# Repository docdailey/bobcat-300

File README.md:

# bobcat-300

Repurposing the **Bobcat Miner 300** (board **G285-V1.0**, Rockchip **RK3566**, mini-PCIe LoRa concentrator) from a
Helium hotspot into an open, hackable LoRa node for **time transfer** experiments, the goal being two-way LoRa
time transfer between nodes, validated against GNSS PPS.

*The [stack adapter](stack-adapter/): plugs into the G285 concentrator socket and carries a RAK5146 (SX1303 + GPS) on top.*

Everything here is fact-checked. Every claim in `docs/` ends with a tag:

- **[VERIFIED: source]**: checked against a primary source (code, device tree, datasheet, logic-analyzer capture, meter
  reading or command output, named in the tag)
- **[UNVERIFIED: origin]**: from notes, community pages or inference, not yet confirmed
- **[CONTRADICTED: what disagrees]**: sources disagree; both sides recorded

Each doc ends with a *Contradictions & open questions* section. Corrections are welcome (open an issue with evidence).

## Contents

| Doc | What it covers |
|---|---|
| [docs/os-boot-gpio.md](docs/os-boot-gpio.md) | Armbian on SD (eMMC untouched), boot chain and boot-script gotchas, 1.5 Mbaud debug console, Ethernet (YT8512B) and Wi-Fi quirks, radio power/reset GPIOs, SPI1, SARADC, broken DT nodes, RTC, PTP |
| [docs/bare-metal-rust.md](docs/bare-metal-rust.md) | Bare-metal Rust image for the RK3566 (QEMU-tested), the carved-core-3 Rust PPS engine that runs on hardware, the deployed Linux time-transfer logger, measured results and lessons |
| [docs/gnss-populate.md](docs/gnss-populate.md) | The unpopulated u-blox NEO-footprint GNSS site: pinout, parts to fit and where, antenna path, PPS routing, beep-test results, install plan, risks |
| [docs/socket-pinout-rak5146.md](docs/socket-pinout-rak5146.md) | The **non-standard** concentrator socket pinout (proven with a logic analyzer), why a RAK5146 reads `0xFF` in a stock G285, and the interposer spec |
| [docs/pps-uart-qerr.md](docs/pps-uart-qerr.md) | GPS PPS to the processor (R47P → GPIO4_D0) and its core-3 capture, the RAK GPS UART (pins 31/33, unmapped), and qErr sawtooth correction |
| [stack-adapter/](stack-adapter/) | **Rev B:** Mini Card-sized stack adapter that lets a RAK5146 (SX1303 + GPS) run in the G285 socket; the RAK stacks right on top (routed, DRC-clean review release) |
| [interposer-rev-a/](interposer-rev-a/) | Rev A breakout interposer (50 × 109.5 mm, superseded by the stack adapter) |
| [tools/](tools/) | Small scripts used for the work (see below) |

## Key facts at a glance

- **Concentrator socket SPI (G285):** SCK = **3**, MISO = **5**, MOSI = **6**, CS = **7**. A RAK2287/RAK5146-style card
  expects 45/47/49/51, so it cannot talk in a stock G285 without rerouting. Power (2/24/39/41/52) and ground match.
- **Radio control GPIOs (Linux sysfs numbers on the Armbian 6.18 image):** 125 = GPIO3_D5 RF enable, 122 = GPIO3_D2 power,
  149 = GPIO4_C5 reset. SPI1 (`spi1m1`) → `/dev/spidev1.0`.
- **Debug console:** UART2 at **1,500,000 baud** (not 115200).
- **Stock card:** N3504S (SX1302 + 2× SX1250). SX1302 has no fine timestamp; SX1303 (e.g. RAK5146) does.
- **GNSS:** an empty 24-pad u-blox NEO footprint whose TIMEPULSE pad reaches socket pin 19 through an unfitted resistor.
  **Do not bridge it if a RAK5146 is fitted**, because its GPS drives pin 19 itself.

## Tools

| File | Purpose |
|---|---|
| `tools/reset_lgw.sh` | Radio power/reset sequence for the G285, matching the stock firmware (used by Semtech `sx1302_hal`) |
| `tools/hal-bobcat.patch` | `sx1302_hal` V2.1.0 patch: runs without the STTS751 temperature sensor the G285 lacks, and prints the chip model (SX1302 vs SX1303) |
| `tools/pinscan.py` | Read-only GPIO input scanner (reads each bank's input register via `/dev/mem`) to map pads to SoC pins |
| `tools/stim.py` | Logic-analyzer stimulus: SPI1 test pattern bursts plus a slow reset toggle |
| `tools/chiploop.sh` | Repeated `chip_id` reads for capturing live MISO traffic |

## Safety

- Work with the stock eMMC untouched: boot Armbian from SD. Pull the card to get the stock firmware back.
- The concentrator can transmit at up to 27 dBm. Keep an antenna or load attached, and observe your local regulations.
- Socket tails are 0.8 mm pitch. Power off before probing with anything that can bridge pins.

## Credits and references

- Armbian image for the G285: sicXnull/Bobcat-Armbian.
- Community pinout reference: helium-repurposed.deobfuscated.org, *Devices / Bobber / Bobcat Miner 300*.
- Semtech `sx1302_hal`; RAKwireless RAK5146 datasheet; u-blox NEO-M8 datasheet and hardware integration manual.

## License

MIT (see [LICENSE](LICENSE)), except `tools/hal-bobcat.patch`, which modifies Semtech's `sx1302_hal` and stays under
Semtech's Revised BSD License.

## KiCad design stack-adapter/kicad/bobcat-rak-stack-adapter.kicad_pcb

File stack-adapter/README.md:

# G285 → RAK5146 stack adapter (rev B)

**Status: routed and KiCad-DRC-clean (review release, 2026-10-22). Not yet fabricated or tested; check everything before ordering.**

A Mini Card-sized stack adapter. Its gold fingers plug into the Bobcat G285 concentrator socket. A mini-PCIe socket sits on top,
right behind the fingers, so the RAK5146 card lies directly above the adapter, over the Bobcat's own card area. There is no
breakout and no jumper field. Rev A, the large breakout interposer, is in [../interposer-rev-a/](../interposer-rev-a/).

## Why

The G285 socket carries SPI on pins 3/5/6/7. RAK's cards expect it on 45/47/49/51. The pinout was proven with a logic
analyzer; see [../docs/socket-pinout-rak5146.md](../docs/socket-pinout-rak5146.md).

## Electrical

| Bobcat (fingers) | RAK5146 (socket J1) | Treatment |
|---|---|---|
| 3 SCK | 45 | rerouted |
| 5 MISO | 47 | rerouted |
| 6 MOSI | 49 | rerouted |
| 7 CS | 51 | rerouted |
| 2, 24, 39, 41, 52 | same | 3.3 V, all tied, 0.25 mm traces |
| 4, 9, 15, 18, 21, 26, 27, 29, 34, 35, 37, 40, 43, 50 | same + socket tabs | GND, routed plus F/B pours, 131 stitching vias |
| 22 | 22 (RAK reset, active high) | straight through (sits low = RAK running) |
| **47** (SoC GPIO4_D0) | **19** (RAK GPS PPS out, 3.3 V) | **GPS PPS via R47P, 0R, FITTED** |
| 45 (SoC GPIO4_C7) | 19 (RAK GPS PPS out) | alternate PPS via R45P, 0R, DNP |
| 19 | 19 | **not connected.** DNP 0R option R19 (straight through) |
| 23 | 23 (RAK GPS reset in) | **not connected.** DNP 0R option R23 |
| 30, 31, 32, 33 | same (RAK GPS I2C / UART) | not connected. DNP 0R options R30–R33 |
| everything else | — | not connected on either side |

**GPS PPS: RAK19 → R47P → finger 47 → GPIO4_D0.**
- The GMAC1 PHC has no programmable pins (`pps_available=0`), so PPS has to land on a SoC GPIO.
- Bobcat socket pins 45 and 47 are spare SoC inputs (GPIO4_C7 / GPIO4_D0). That was verified by a read-only EXT_PORT scan with a
  1 kΩ pull on 2026-10-22.
- On the adapter, fingers 45 and 47 are their own nets (F45, F47). They are **not** the RAK's 45/47: those come from the SPI
  reroute of fingers 3 and 5.
- With R19 and R45P open, the RAK-19 net is exactly J1.19, R47P, R45P and R19. Only R47P is fitted, so it reaches finger 47 and
  nothing else (checked on the final netlist). Fit R45P instead of R47P to use GPIO4_C7.

All links are 0402 0R, UNI-ROYAL 0402WGF0000TCE (LCSC C17168, a JLCPCB basic part). On every link, pad 1 is the Bobcat finger and
pad 2 the RAK socket pin.

## Mechanical (all distances from the finger edge)

| Item | Value | Source |
|---|---|---|
| Outline | **60.30 × 30.00 mm**, 31.30 mm across the socket-tab ears (3.20–7.90 mm) | this design |
| Thickness / fingers | 1.0 mm, contacts 0.60 × 2.55 on 0.80, odd contacts on top (verified on a real card) | PCI-SIG Mini CEM 1.2 |
| Bobcat hold-down holes | Ø2.6 at **48.05**, x ±12.10 | Mini CEM fig 2-3 |
| RAK socket J1 | SOFNG PCIE-52P52H (LCSC C444927), top side; pin N at the same x as finger N | |
| J1 card-edge line (where the RAK card's edge seats; the peg line) | **9.30** | footprint + Mini CEM host-socket datum |
| J1 front (odd-row pads, solder tabs) | **4.20**, i.e. **1.65 mm past the 2.55 mm fingers**; J1 body from 5.50 | see "How close" |
| RAK standoff holes | Ø2.4 NPTH at **57.35** (9.30 + 48.05), x ±12.10 | Mini CEM fig 2-3 |
| RAK card far end | 9.30 + 50.95 = **60.25** | |
| Hold-down keep-outs | 5.8 × 5.8 mm, all layers, at every hole | Mini CEM fig 2-7 |
| Bottom side | flat: no components, fingers + routing + GND only | |

**How close the socket can sit to the fingers.** Three limits apply. The third one binds:

1. **Spec.** Mini CEM 1.2 fig 2-7 has a top-side "component keep out area for connector" of **3.20 mm MIN** from the edge, and
   4.20 mm only behind the key slot. Fig 2-9 shows the host connector housing reaching 3.20 mm MAX onto the card.
2. **Fab.** JLCPCB's gold-finger rules set no finger-to-pad spacing. They require only:
   - a full solder-mask opening on the fingers
   - no copper in the bevel
   - the 50 mm minimum size

   The fab profile's general rules still apply: 0.127 mm pad to pad, 0.30 mm copper to edge. J1's solder tabs sit over the
   card's corner notches (edge at 3.20 mm), so the tab front must be at ≥ 3.50 mm. That gives S ≥ 8.6 mm.
3. **Routing escape (binding).** These top fingers have to leave sideways:
   - SPI 3/5/7
   - the PPS fingers 45/47
   - the option fingers 19/23/31/33

   Each needs a via between its end (2.55 mm) and J1's pads, and the bottom fingers' traces (MOSI 6) must pass between those
   vias. Freerouting completes at **S = 9.30** (pads at 4.20). At S = 9.1 / 9.0 / 8.8 / 8.6 it leaves 1 / 1 / 4 / 4 nets
   unrouted after pours.

   Pre-placing the escape vias in a 0.95 mm gap was also tried. Those through vias land among the bottom fingers and wall in
   MOSI 6, so it doesn't work.

**Fit inside the G285.** The space measured past a stock card is 17 mm, so the stack must end within 50.95 + 17 = 67.95 mm of the
finger edge. Seating depth is already inside the numbers above:

- The adapter's fingers seat in the Bobcat socket exactly like the stock card. The 48.05 mm hold-down distance is measured from
  that same seated edge, so there is no offset.
- The RAK card's edge seats in J1 at the card-edge line, 9.30 mm. Its first few mm are inside the J1 body, and it ends at
  9.30 + 50.95 = 60.25 mm.

The stack therefore ends at **60.30 mm** (the outline; the RAK card at 60.25). That is 9.35 mm past a stock card and 7.65 mm inside
the 67.95 mm limit.

**Heights.**

- J1 holds the RAK card plane at 3.25 mm, so the card's underside is 2.75 mm above the adapter.
- RAK standoffs: **M2, 2.75 mm** (or a 2.5 mm M2 SMT/press standoff plus a 0.25 mm washer).
- The Bobcat hold-down screws at 48.05 sit under the RAK card. An M2 pan or wafer head of ≤ 1.6 mm clears the 2.75 mm gap.
- J1's two plastic pegs (Ø1.8 / Ø1.3 NPTH at 9.30) poke ~0.6 mm out of the bottom. Check them against the G285 board under the
  card; trim them flush if they touch.
- No Z conflict with the Bobcat socket. Its housing covers the card only inside the 3.20 mm keep-out (4.20 at the key), and every
  part of J1 starts at 4.20 mm or more.

**Paper fit check.** Print [renders/bobcat-rak-stack-adapter-1to1-fitcheck.pdf](renders/bobcat-rak-stack-adapter-1to1-fitcheck.pdf)
at 100% (A4 page) and confirm that the bar reads 50.00 mm. The page has the outline, holes, J1 footprint and courtyard, and the
dimensions above as text. Also check the ears against the Bobcat socket's side latches.

## Fabrication: JLCPCB gold fingers on a 30 mm card

JLCPCB does not accept a board this size with gold fingers as a single board:

- The length and width of a single board **or panel** with gold fingers must each be ≥ 50 mm, and chamfers are not offered under
  5 × 5 cm.
- Fingers on a V-cut panel cannot be bevelled.
- Only ENIG gives gold fingers.
- The finger area gets a full solder-mask opening, and the bevel zone must hold no copper. This board keeps a 1.0 mm no-copper
  strip, except the fingers.
- With a 30° bevel on 1.0 mm, the bevel reaches ≈ 0.43 mm in: L = (1.0/2 − 0.5/2)/tan 30°.

Sources: [JLCPCB: gold fingers](https://jlcpcb.com/help/article/jlcpcb-gold-fingers),
[JLCPCB order FAQ: gold fingers](https://jlcpcb.com/quote/pcbOrderFaq/Gold%20Fingers).

**The order uses the 2-up panel in [fab/panel/](fab/panel/)** (built with KiKit 1.8.1 and a small framing plugin, `panel_framing.py`;
`make_panel.sh` rebuilds it):

- **Layout:** two boards side by side, finger edges flush on the panel's bottom edge. That edge carries nothing else: no rail,
  no tab, no V-cut.
- **Rails:** 5 mm rails on the left and right, and a top rail (8 mm, opposite the fingers). The panel is **78.6 × 70.5 mm**
  (78.7 × 70.6 in the Gerbers), which meets JLCPCB Standard PCBA's ≥ 70 mm on each side.
- **Tabs:** mouse-bites, 3 mm wide, 0.5 mm NPTH at 1.0 mm pitch: two per long side and two per board on the top edge.
- **Fiducials:** 3 fiducials (1 mm copper, 2 mm opening) on the side rails, 10 mm from the top and bottom edges.
- **Tooling holes:** 4 × Ø2.0 at the corners, 5 mm from the top and bottom edges.
- **Checks:** KiCad DRC 0 errors and 0 unconnected; the 104 finger-pad edge findings are the card-edge override, 52 per board.
  gerber_check (jlcpcb-2layer-cardedge): **all pass, including outline**.

GND stitching vias keep 1.0 mm from the board outline, so they stay clear of the mouse-bites.

**JLCPCB / JLCONE order options**

PCB:

| Option | Setting |
|---|---|
| Base material | FR-4 |
| Layers | 2 |
| Dimensions | 78.6 × 70.5 mm |
| PCB qty | 5 panels (= 10 boards; 5 is JLC's minimum) |
| Product type | industrial/consumer |
| Different design | 1 |
| Delivery format | **Panel by Customer**, 2 × 1 = 2 pcs/panel, break-away = **mouse-bites / tab-route** (no V-cut) |
| Thickness | **1.0 mm** |
| Color | any (green is the cheapest) |
| Surface finish | **ENIG** |
| Gold fingers | **Yes** |
| Bevel | **30°**, on the finger edge (the bottom edge of the panel) |
| Copper weight | 1 oz |
| Via covering | tented |
| Remove order number | as preferred |
| Castellated / impedance | no |

PCBA:

| Option | Setting |
|---|---|
| Type | **Standard** (JLCPCB disables Economic with ENIG / gold fingers) |
| Side | **Top** |
| Qty | **3 panels = 6 boards** (≥ 5) |
| Tooling holes | added by customer |
| Edge rails / fiducials | already on the panel; don't add more |
| Files | `fab/panel/bobcat-rak-stack-adapter-panel-bom.csv` and `-cpl.csv` |

- **BOM:** J1_0, J1_1 = C444927 (SOFNG PCIE-52P52H, Extended, offered for Economic and Standard); R47P_0, R47P_1 = C17168 (0R 0402, Basic). Every other footprint is DNP and left out.
- **Economic vs Standard:** Standard. JLCPCB offers no Economic assembly with ENIG/gold fingers, and Standard needs ≥ 70 mm per side, which the top rail provides.
  time for nothing on this board.

**J1 rotation in JLCPCB's preview.** The KiCad footprint *is* the EasyEDA/JLC footprint for C444927 (imported unchanged), placed at
180°. The CPL's 180° therefore puts JLC's model in the same frame. In the preview, check three things:
- The socket body sits over both pad rows, with its card slot opening toward the board's hold-down holes, away from the gold fingers.
- The **larger Ø1.8 peg is on the left** (fingers at the bottom) and the Ø1.3 peg on the right. The pegs are asymmetric, so a wrong
  rotation shows up as pegs off their holes.
- R47P sits at 270° on its two pads, left of the option row.

If the preview shows the pegs swapped or the body off the pads, set J1 to 0° there; don't edit the files.

Sources: [JLCPCB: edge rails and fiducials for assembly](https://jlcpcb.com/help/article/how-to-add-edge-rails-fiducials-for-pcb-assembly-order),
[JLCPCB: process edges and positioning holes](https://jlcpcb.com/help/article/specifications-for-adding-process-edges-and-positioning-holes),
[JLCPCB assembly capabilities](https://jlcpcb.com/capabilities/pcb-assembly-capabilities),
[C444927](https://jlcpcb.com/partdetail/C444927).

The single board's REVIEW zip in `fab/` fails `outline` (31.4 × 60.4 mm < 50 × 50) by design and is for review only. Order the panel.

## Design status (2026-10-22)

The design starts in a tscircuit-based board pipeline (pcb-factory, board `bobcat-rak-stack-adapter`, branch
`bobcat-rak-interposer`). It is finished in KiCad by scripts, never by mouse; the scripts are in `pipeline/`:

1. `fix_export.py` repairs the tscircuit → KiCad export:
   - the even fingers go back to B.Cu, and the thickness is set to 1.0 mm
   - GND pours, the bevel strip and the hold-down keep-outs are added
   - part data is set: R47P is fitted, the other links are DNP
   - the holes become MH1–MH4, and the J1 silk is kept off the edge
   - the J1 3D model goes on, and the scale bar and dimension notes go on the fit-check page
2. `kicad_to_dsn.py` writes the Specctra DSN. Settings:
   - 0.6/0.3 vias
   - signal 0.14 mm, clearance 0.13 mm, 3V3 0.25 mm
   - via-to-via and peg keep-outs sized so drills stay ≥ 0.5 mm apart
3. Freerouting 2.4.1 (150 passes) gave 0 unrouted after pours (`pipeline/freerouting.log`).
4. `ses_to_kicad.py` imports the routes.
5. `space_vias.py` restores 0.5 mm drill spacing if any via pair is closer; nothing needed moving on this route.
6. `stitch_gnd.py` places 131 stitching vias, each ≥ 1.0 mm from the outline, (grid, then targeted fragments, then a prune of floating ones). Zone refills are
   done by `kicad-cli` between passes.
7. `run_pipeline.sh` runs steps 4–6; `export.sh` makes the package.

Results:

- **KiCad DRC (kicad-cli 10.0.4): 0 errors, 0 unconnected.**
  - The 52 `copper_edge_clearance` findings are on the finger pads only. They are exempted and itemised by the fab profile's
    named `card_edge` override.
  - 15 `lib_footprint_issues` warnings remain: the exported footprints are not from a KiCad library.
- **gerber_check (jlcpcb-2layer-cardedge): all pass except `outline`** (see Fabrication). The values:
  - 2 copper layers
  - min drill 0.30 mm
  - closest drill pair 0.507 mm (limit 0.50)
  - drill to edge 1.4 mm
  - no orphan paste
  - min aperture 0.14 mm
- **Factory loop.** Every hard gate passes. The loop stops on the soft gate `completeness ≥ 3.0` (Jev 2.98) with `edit_source` and
  names no defect, the same as rev A. It is **not export_ready**, and the fab zip here was made with kicad-cli directly and is
  marked REVIEW. Nothing has been ordered or uploaded.
- Routing: 355 track segments, 45 routed vias, 131 GND stitching vias.

## Files

- `kicad/`: the KiCad 10 project (`bobcat-rak-stack-adapter.kicad_pcb` / `.kicad_pro` / `.kicad_sch`, the factory's source for
  this board). It also holds `3dmodels/PCIE-52P52H_C444927.step`, the SOFNG socket model from EasyEDA/LCSC.
- `fab/`:
  - `bobcat-rak-stack-adapter-REVIEW-gerbers.zip`: Gerbers, PTH/NPTH Excellon and drill maps, single board, not panelised
  - the KiCad DRC and gerber_check JSON
  - BOM and CPL: J1 and R47P are populated; R19, R23, R30–R33 and R45P are DNP. **Check J1's rotation in JLCPCB's placement
    preview**, because EasyEDA-derived parts often need a 180° correction.
- `renders/`:
  - 3D views (iso, top, bottom, a socket close-up)
  - flat top/bottom copper and the schematic (SVG + PNG)
  - the 1:1 fit-check PDF
- `pipeline/`: the scripts above, `index.tsx` (the board source as committed in pcb-factory) and the Freerouting log. To rebuild:
  1. Put the exported `bobcat-rak-stack-adapter.kicad_*` in a work dir next to the scripts.
  2. `run_pipeline.sh dsn`
  3. Run Freerouting on `fixed.dsn` to make `fixed.ses`.
  4. `run_pipeline.sh`
  5. `export.sh` (it writes to the parent of the work dir).

## Assembly order

1. Solder J1 and R47P (or have JLCPCB place them). Leave R19, R23, R30–R33 and R45P empty.
2. Fit two M2 × 2.75 mm standoffs at the RAK holes (57.35 mm).
3. Plug the adapter into the G285 socket and screw it down at 48.05 mm with low-head M2 screws.
4. Insert the RAK5146 into J1 at an angle, press it down onto the standoffs and screw it down.
5. Run `chip_id`; expect a real version byte, not `0xFF`. GPS PPS then arrives on GPIO4_D0.

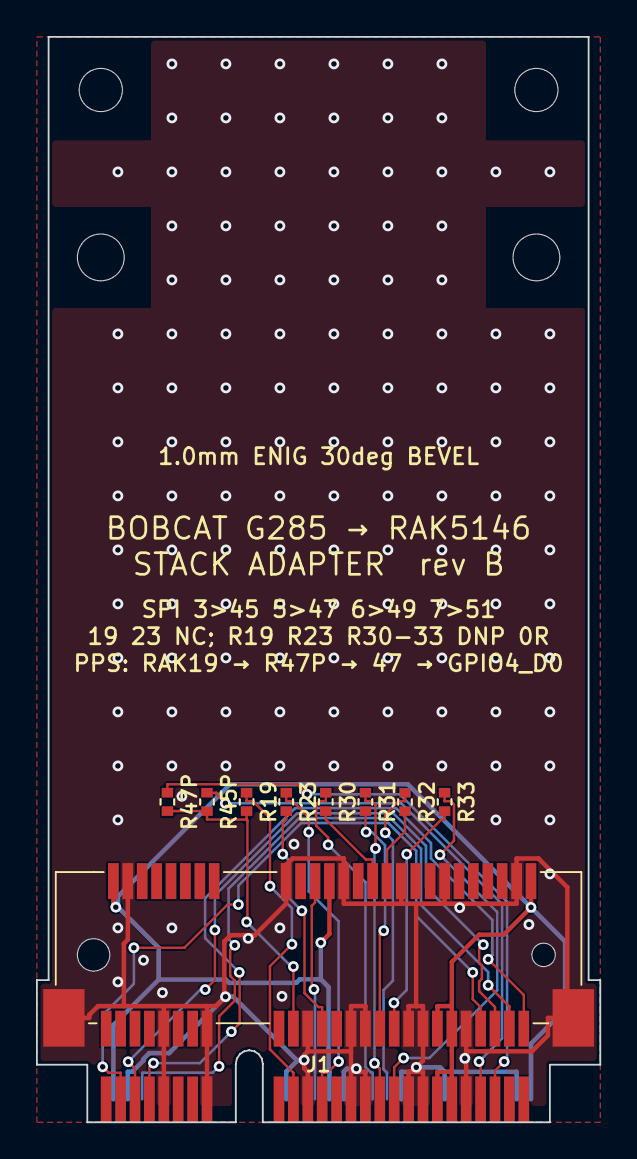
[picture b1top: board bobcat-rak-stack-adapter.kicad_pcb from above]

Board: 2 copper layers, 31.3 x 60.3 mm, 15 parts (0 on the bottom side), 21 nets.

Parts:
CE1, CE2: card edge; PCIe_Mini_Card_edge_PCI-SIG_Mini_CEM_1_2
J1: PCIE-52P52H
MH1, MH2: Bobcat hold-down 2.6mm; hole_circle_holeDiameter2.6mm
MH3, MH4: RAK standoff M2 2.4mm; hole_circle_holeDiameter2.4mm
R19, R23, R30, R31, R32, R33, R45P: 0R DNP; resistor_res0402
R47P: 0R; resistor_res0402

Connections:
B19: CE2.19, R19.1
B23: CE2.23, R23.1
B30: CE2.30, R30.1
B31: CE2.31, R31.1
B32: CE2.32, R32.1
B33: CE2.33, R33.1
F45: CE2.45, R45P.1
F47: CE2.47, R47P.1
GND: CE1.4, CE1.9, CE1.15, CE2.18, CE2.21, CE2.26, CE2.27, CE2.29, CE2.34, CE2.35, CE2.37, CE2.40, CE2.43, CE2.50, J1.4, J1.9, J1.15, J1.18, J1.21, J1.26, J1.27, J1.29, J1.34, J1.35, J1.37, J1.40, J1.43, J1.50, J1.53, J1.54
R19: J1.19, R19.2, R45P.2, R47P.2
R23: J1.23, R23.2
R30: J1.30, R30.2
R31: J1.31, R31.2
R32: J1.32, R32.2
R33: J1.33, R33.2
RST22: CE2.22, J1.22
SPI_3_45: CE1.3, J1.45
SPI_5_47: CE1.5, J1.47
SPI_6_49: CE1.6, J1.49
SPI_7_51: CE1.7, J1.51
V3V3: CE1.2, CE2.24, CE2.39, CE2.41, CE2.52, J1.2, J1.24, J1.39, J1.41, J1.52

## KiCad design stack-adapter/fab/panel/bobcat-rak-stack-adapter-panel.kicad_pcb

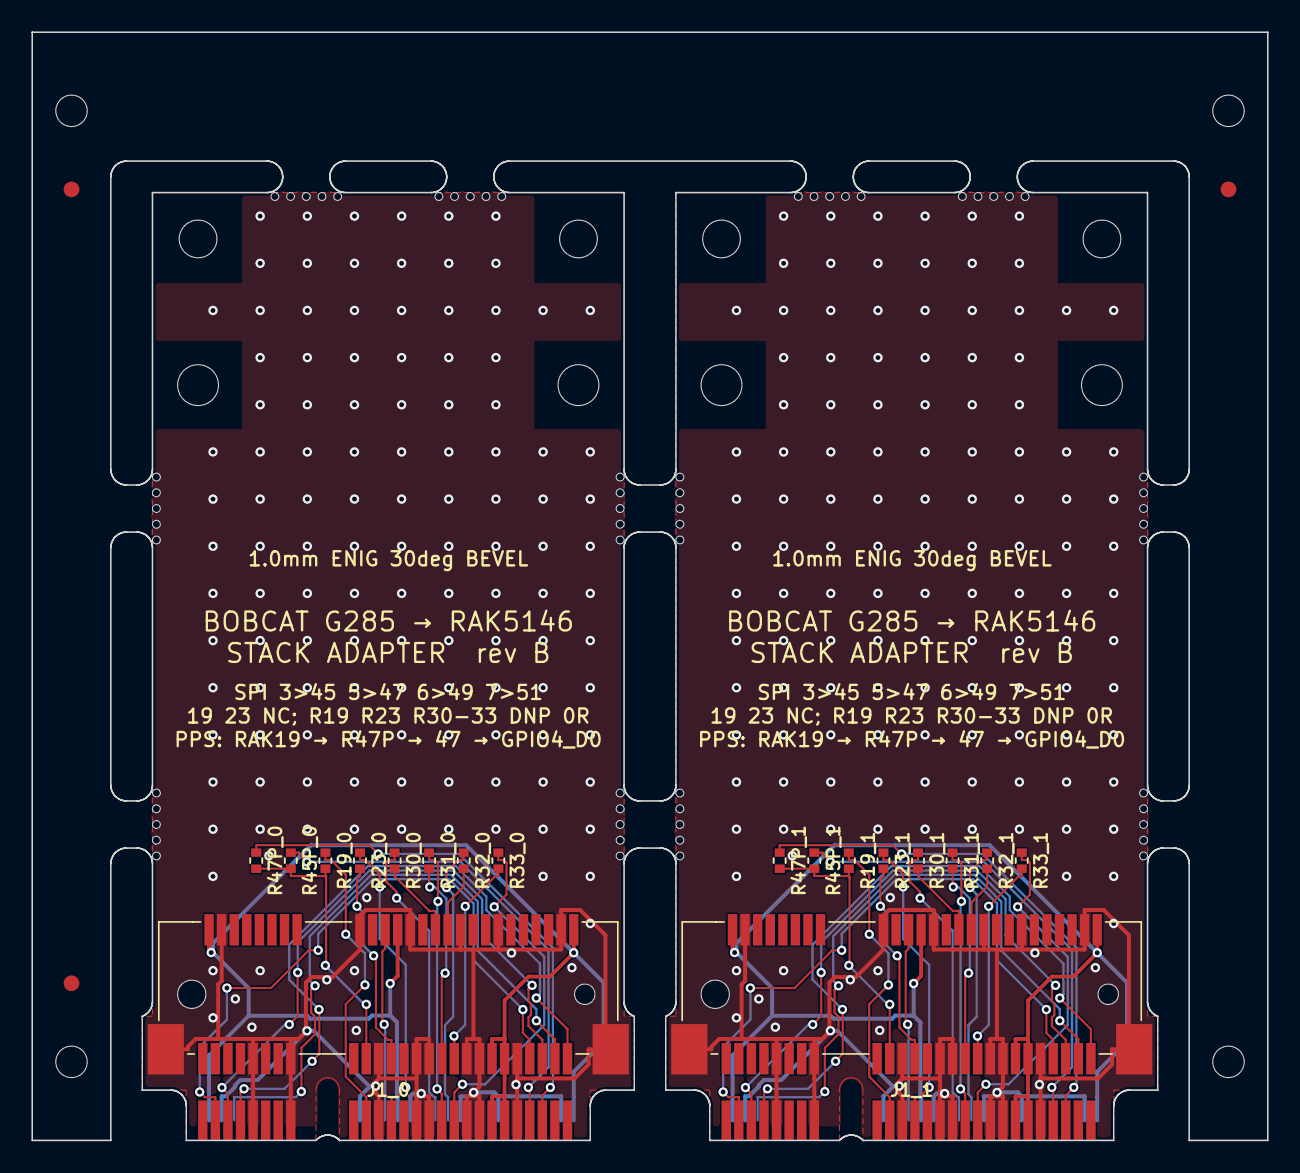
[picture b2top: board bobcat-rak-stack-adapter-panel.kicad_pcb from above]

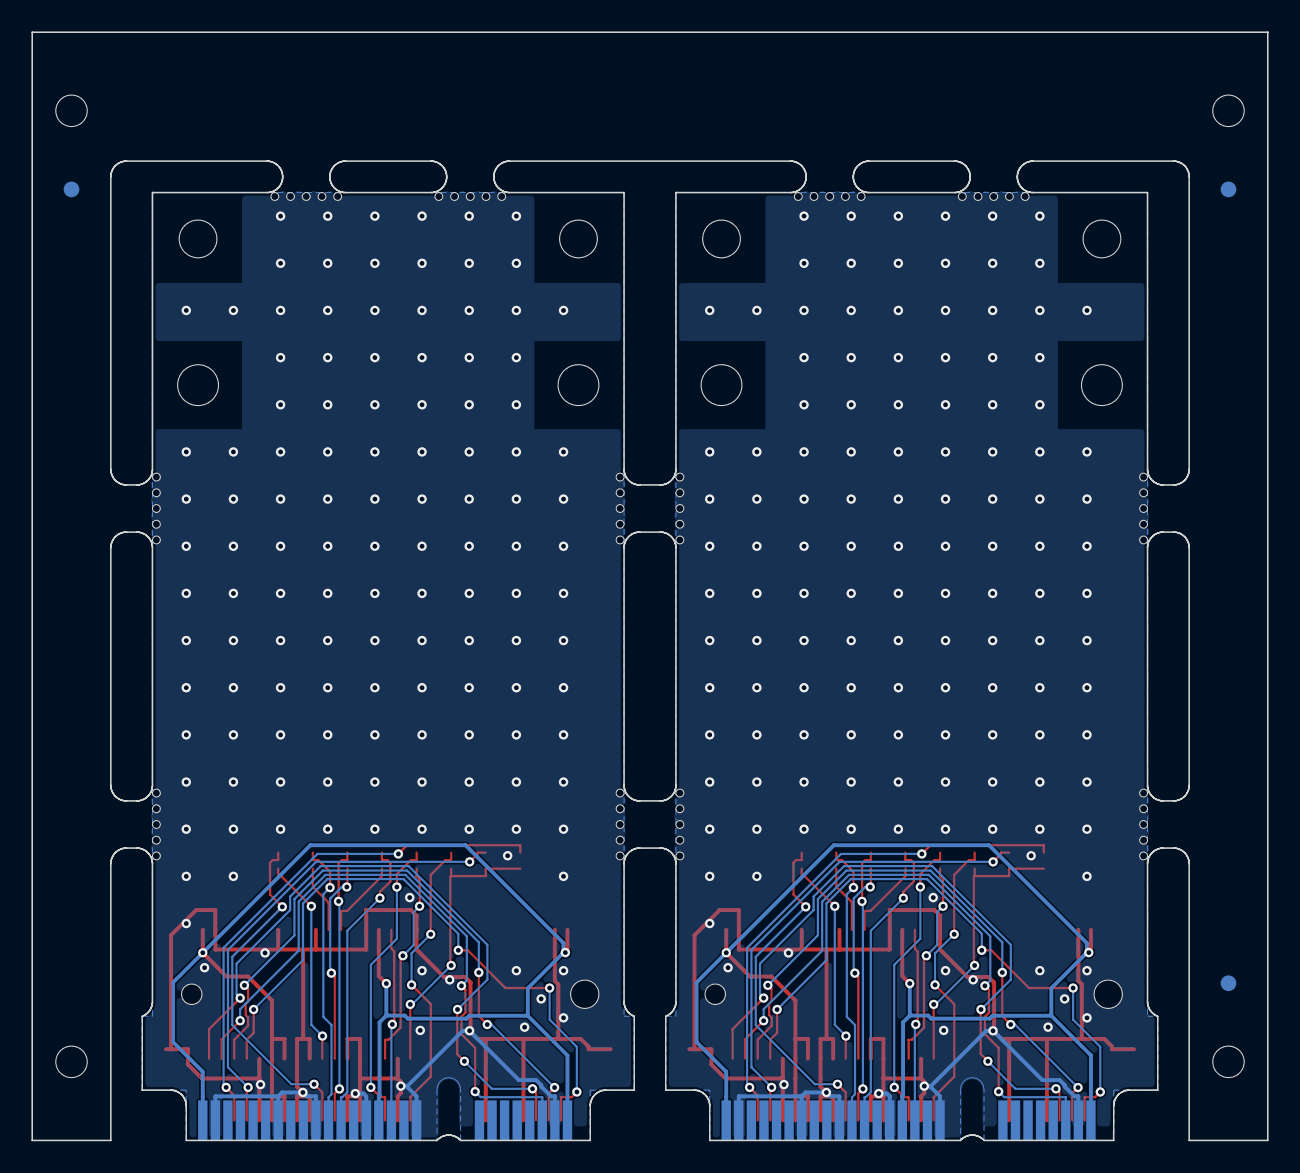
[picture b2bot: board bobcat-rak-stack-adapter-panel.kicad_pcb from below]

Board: 2 copper layers, 78.6 x 70.5 mm, 100 parts (3 on the bottom side), 42 nets.

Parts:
CE1_0, CE1_1, CE2_0, CE2_1: card edge; PCIe_Mini_Card_edge_PCI-SIG_Mini_CEM_1_2
J1_0, J1_1: PCIE-52P52H
KiKit_FID_B_1, KiKit_FID_B_2, KiKit_FID_B_3: Fiducial
KiKit_FID_T_1, KiKit_FID_T_2, KiKit_FID_T_3: Fiducial
KiKit_MB_1_1, KiKit_MB_1_2, KiKit_MB_1_3, KiKit_MB_1_4, KiKit_MB_1_5, KiKit_MB_2_1, KiKit_MB_2_2, KiKit_MB_2_3, KiKit_MB_2_4, KiKit_MB_2_5, KiKit_MB_3_1, KiKit_MB_3_2, KiKit_MB_3_3, KiKit_MB_3_4, KiKit_MB_3_5, KiKit_MB_4_1, KiKit_MB_4_2, KiKit_MB_4_3, KiKit_MB_4_4, KiKit_MB_4_5, KiKit_MB_5_1, KiKit_MB_5_2, KiKit_MB_5_3, KiKit_MB_5_4, KiKit_MB_5_5, KiKit_MB_6_1, KiKit_MB_6_2, KiKit_MB_6_3, KiKit_MB_6_4, KiKit_MB_6_5, KiKit_MB_7_1, KiKit_MB_7_2, KiKit_MB_7_3, KiKit_MB_7_4, KiKit_MB_7_5, KiKit_MB_8_1, KiKit_MB_8_2, KiKit_MB_8_3, KiKit_MB_8_4, KiKit_MB_8_5, KiKit_MB_9_1, KiKit_MB_9_2, KiKit_MB_9_3, KiKit_MB_9_4, KiKit_MB_9_5, KiKit_MB_10_1, KiKit_MB_10_2, KiKit_MB_10_3, KiKit_MB_10_4, KiKit_MB_10_5, KiKit_MB_11_1, KiKit_MB_11_2, KiKit_MB_11_3, KiKit_MB_11_4, KiKit_MB_11_5, KiKit_MB_12_1, KiKit_MB_12_2, KiKit_MB_12_3, KiKit_MB_12_4, KiKit_MB_12_5: NPTH
KiKit_TO_1, KiKit_TO_2, KiKit_TO_3, KiKit_TO_4: NPTH
MH1_0, MH1_1, MH2_0, MH2_1: Bobcat hold-down 2.6mm; hole_circle_holeDiameter2.6mm
MH3_0, MH3_1, MH4_0, MH4_1: RAK standoff M2 2.4mm; hole_circle_holeDiameter2.4mm
R19_0, R19_1, R23_0, R23_1, R30_0, R30_1, R31_0, R31_1, R32_0, R32_1, R33_0, R33_1, R45P_0, R45P_1: 0R DNP; resistor_res0402
R47P_0, R47P_1: 0R; resistor_res0402

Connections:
Board_0-B19: CE2_0.19, R19_0.1
Board_0-B23: CE2_0.23, R23_0.1
Board_0-B30: CE2_0.30, R30_0.1
Board_0-B31: CE2_0.31, R31_0.1
Board_0-B32: CE2_0.32, R32_0.1
Board_0-B33: CE2_0.33, R33_0.1
Board_0-F45: CE2_0.45, R45P_0.1
Board_0-F47: CE2_0.47, R47P_0.1
Board_0-GND: CE1_0.4, CE1_0.9, CE1_0.15, CE2_0.18, CE2_0.21, CE2_0.26, CE2_0.27, CE2_0.29, CE2_0.34, CE2_0.35, CE2_0.37, CE2_0.40, CE2_0.43, CE2_0.50, J1_0.4, J1_0.9, J1_0.15, J1_0.18, J1_0.21, J1_0.26, J1_0.27, J1_0.29, J1_0.34, J1_0.35, J1_0.37, J1_0.40, J1_0.43, J1_0.50, J1_0.53, J1_0.54
Board_0-R19: J1_0.19, R19_0.2, R45P_0.2, R47P_0.2
Board_0-R23: J1_0.23, R23_0.2
Board_0-R30: J1_0.30, R30_0.2
Board_0-R31: J1_0.31, R31_0.2
Board_0-R32: J1_0.32, R32_0.2
Board_0-R33: J1_0.33, R33_0.2
Board_0-RST22: CE2_0.22, J1_0.22
Board_0-SPI_3_45: CE1_0.3, J1_0.45
Board_0-SPI_5_47: CE1_0.5, J1_0.47
Board_0-SPI_6_49: CE1_0.6, J1_0.49
Board_0-SPI_7_51: CE1_0.7, J1_0.51
Board_0-V3V3: CE1_0.2, CE2_0.24, CE2_0.39, CE2_0.41, CE2_0.52, J1_0.2, J1_0.24, J1_0.39, J1_0.41, J1_0.52
Board_1-B19: CE2_1.19, R19_1.1
Board_1-B23: CE2_1.23, R23_1.1
Board_1-B30: CE2_1.30, R30_1.1
Board_1-B31: CE2_1.31, R31_1.1
Board_1-B32: CE2_1.32, R32_1.1
Board_1-B33: CE2_1.33, R33_1.1
Board_1-F45: CE2_1.45, R45P_1.1
Board_1-F47: CE2_1.47, R47P_1.1
Board_1-GND: CE1_1.4, CE1_1.9, CE1_1.15, CE2_1.18, CE2_1.21, CE2_1.26, CE2_1.27, CE2_1.29, CE2_1.34, CE2_1.35, CE2_1.37, CE2_1.40, CE2_1.43, CE2_1.50, J1_1.4, J1_1.9, J1_1.15, J1_1.18, J1_1.21, J1_1.26, J1_1.27, J1_1.29, J1_1.34, J1_1.35, J1_1.37, J1_1.40, J1_1.43, J1_1.50, J1_1.53, J1_1.54
Board_1-R19: J1_1.19, R19_1.2, R45P_1.2, R47P_1.2
Board_1-R23: J1_1.23, R23_1.2
Board_1-R30: J1_1.30, R30_1.2
Board_1-R31: J1_1.31, R31_1.2
Board_1-R32: J1_1.32, R32_1.2
Board_1-R33: J1_1.33, R33_1.2
Board_1-RST22: CE2_1.22, J1_1.22
Board_1-SPI_3_45: CE1_1.3, J1_1.45
Board_1-SPI_5_47: CE1_1.5, J1_1.47
Board_1-SPI_6_49: CE1_1.6, J1_1.49
Board_1-SPI_7_51: CE1_1.7, J1_1.51
Board_1-V3V3: CE1_1.2, CE2_1.24, CE2_1.39, CE2_1.41, CE2_1.52, J1_1.2, J1_1.24, J1_1.39, J1_1.41, J1_1.52

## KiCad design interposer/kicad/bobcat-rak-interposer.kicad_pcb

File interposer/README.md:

# G285 → RAK5146 interposer

**Status: routed and KiCad-DRC-clean (review release). Not yet fabricated or tested; check everything before ordering.**

A full-size mini-PCIe card-edge board (1.0 mm, gold fingers) that plugs into the Bobcat G285 concentrator socket, with a
mini-PCIe socket on top for a RAK5146 (SX1303 + ZOE-M8Q GPS, SPI variant).

## Why

The G285 socket carries SPI on pins 3/5/6/7. RAK's cards expect 45/47/49/51. See
[../docs/socket-pinout-rak5146.md](../docs/socket-pinout-rak5146.md).

## Specification

| Bobcat (fingers) | RAK5146 (socket) | Treatment |
|---|---|---|
| 3 SCK | 45 | reroute |
| 5 MISO | 47 | reroute |
| 6 MOSI | 49 | reroute |
| 7 CS | 51 | reroute |
| 19 | 19 (RAK GPS PPS out) | **isolated** |
| 23 | 23 (RAK GPS reset in) | **isolated** |
| 2, 24, 39, 41, 52 | same | 3.3 V straight through |
| all GND | same | straight through |
| 22 | 22 (RAK reset, active high) | straight through (sits low = RAK running) |
| everything else | same | straight through |

- Every pin on 0.1 in. headers behind default-closed solder jumpers, so the board doubles as a breakout/probe board.
- Original pin positions for 3/5/6/7 and 45/47/49/51 are on jumpers, default open, so the reroute can be undone.

Design files, renders and a REVIEW fab package are in this directory (see Files below).

## Design status (2026-10-22)

Drafted in a tscircuit-based board pipeline; **not fab-ready**.

- 4-layer, **1.0 mm** (PCI-SIG Mini Card thickness), ENIG with hard-gold fingers and a 30° bevel. The outline is 50 × 109.5 mm
  because JLCPCB won't bevel fingers on boards under 50 mm, so the board overhangs the G285 by about 58 mm (a bench
  fixture; the lid won't close).
- Card edge per the PCI-SIG Mini Card Electromechanical Spec Rev 1.2: 52 contacts, key, Ø2.6 mm hold-down holes.
- RAK socket: SOFNG PCIE-52P52H (LCSC C444927). The RAK card needs ~3.2 mm M2 standoffs.
- 37 solder jumpers: reroute closed, original 3/5/6/7 ↔ 45/47/49/51 and 19/23 open; two 2×18 breakout headers.
- **Routing complete.** Freerouting (300 passes) on a DSN written from the KiCad board: every signal routed, GND
  through a solid In1.Cu plane plus F/B pours stitched with 193 vias. 1228 track segments, 143 routed vias.
- **KiCad DRC (kicad-cli 10.0.4): 0 errors, 0 unconnected.** The 52 `copper_edge_clearance` findings on the finger
  pads are exempted and itemised by the fab profile's named `card_edge` override. 46 `lib_footprint_issues`
  warnings remain (the exported footprints are not from a KiCad library).
- **gerber_check (jlcpcb-4layer-cardedge): all pass.** 4 copper layers, outline 50.1 × 109.6 mm, min drill 0.2 mm
  (414 holes), closest drill pair 0.402 mm, drill to edge 0.45 mm, no orphan paste, min aperture 0.127 mm.
- **Not factory export_ready.** Every hard gate passes; the factory loop stops at `human` on the soft gate
  `completeness ≥ 3.0` (Jev judged 2.81–2.92 and named no defect). The fab zip here was made with kicad-cli
  directly and is marked REVIEW. Nothing has been ordered or uploaded.
- **Hand fixes, all scripted** (`pipeline/`): the tscircuit→KiCad export put the 26 even fingers on F.Cu, set 1.6 mm,
  mis-layered the pours and keepouts, and modelled the 27 bridged jumpers as cross-net tracks. `fix_export.py`
  corrects each (even fingers back on B.Cu, 1.0 mm, GND zones on F/In1/B with a 1 mm no-copper bevel strip,
  net-tie jumpers, 0.8 mm refdes, J1 MPN/LCSC, DNP flags, MH1–MH4). Then `kicad_to_dsn.py` → Freerouting →
  `ses_to_kicad.py` → `stitch_gnd.py`.
- Finger face orientation checked on a real card (2026-10-22): the top (component) face carries the **odd** contacts. The 5th
  and 8th contacts from the short end on the top face beep to ground = pins 9 and 15, matching the spec and this design. **[VERIFIED: continuity]**

## Files

- `kicad/` KiCad 10 project: `bobcat-rak-interposer.kicad_pcb` / `.kicad_pro` / `.kicad_sch` (the factory's source for this board).
- `fab/` `bobcat-rak-interposer-REVIEW-gerbers.zip` (Gerbers, PTH/NPTH Excellon, drill maps), BOM and CPL (J1 only; everything else is DNP or a board feature).
- `renders/` PCB top, bottom, In1 GND plane and schematic (SVG + PNG).
- `pipeline/`: the conversion and routing scripts (export fixes, KiCad↔Specctra DSN/SES, ground stitching).
- JLCPCB options when approved: 4 layers, 1.0 mm, ENIG, gold fingers, 30° bevel, no V-cut panel, no impedance control.

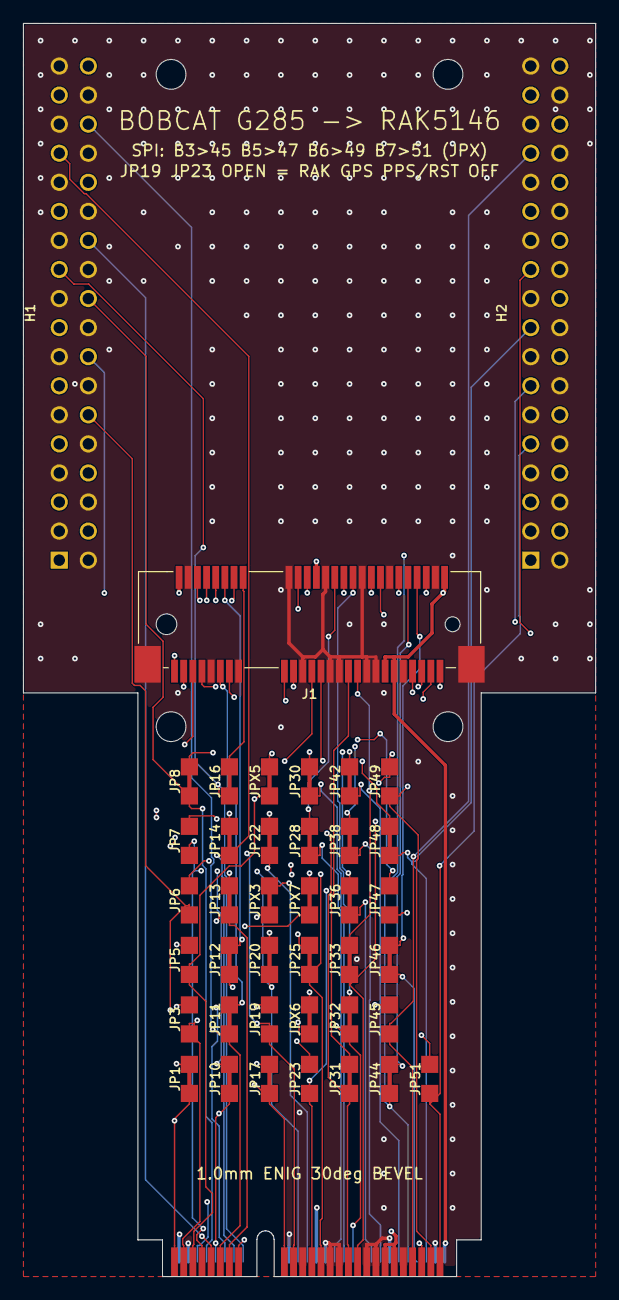
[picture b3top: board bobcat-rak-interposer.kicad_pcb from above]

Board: 4 copper layers, 50.0 x 109.5 mm, 46 parts (0 on the bottom side), 70 nets.

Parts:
CE1, CE2: card edge; PCIe_Mini_Card_edge_PCI-SIG_Mini_CEM_1_2
H1, H2: 2x18 2.54mm header (unpopulated); pin_header_pinrow36_p2_54_nopinlabels_rows2
J1: PCIE-52P52H
JP1, JP8, JP10, JP11, JP12, JP13, JP14, JP16, JP17, JP20, JP22, JP25, JP28, JP30, JP31, JP32, JP33, JP36, JP38, JP42, JP44, JP46, JP48: solder jumper; chip_solderjumper2_bridged12
JP3, JP5, JP6, JP7, JP19, JP23, JP45, JP47, JP49, JP51: solder jumper; chip_solderjumper2
JPX3, JPX5, JPX6, JPX7: solder jumper; chip_solderjumper2_bridged12
MH1, MH2, MH3, MH4: MountingHole 2.6mm; hole_circle_holeDiameter2.6mm

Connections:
B1: CE1.1, H1.1, JP1.1
B3: CE1.3, H1.3, JP3.1, JPX3.1
B5: CE1.5, H1.5, JP5.1, JPX5.1
B6: CE1.6, H1.7, JP6.1, JPX6.1
B7: CE1.7, H1.9, JP7.1, JPX7.1
B8: CE1.8, H1.11, JP8.1
B9: CE1.9, H1.13
B10: CE1.10, H1.15, JP10.1
B11: CE1.11, H1.17, JP11.1
B12: CE1.12, H1.19, JP12.1
B13: CE1.13, H1.21, JP13.1
B14: CE1.14, H1.23, JP14.1
B15: CE1.15, H1.25
B16: CE1.16, H1.27, JP16.1
B17: CE2.17, H1.29, JP17.1
B19: CE2.19, H1.31, JP19.1
B20: CE2.20, H1.33, JP20.1
B22: CE2.22, H1.35, JP22.1
B23: CE2.23, H2.1, JP23.1
B25: CE2.25, H2.3, JP25.1
B28: CE2.28, H2.5, JP28.1
B30: CE2.30, H2.7, JP30.1
B31: CE2.31, H2.9, JP31.1
B32: CE2.32, H2.11, JP32.1
B33: CE2.33, H2.13, JP33.1
B36: CE2.36, H2.15, JP36.1
B38: CE2.38, H2.17, JP38.1
B42: CE2.42, H2.19, JP42.1
B44: CE2.44, H2.21, JP44.1
B45: CE2.45, H2.23, JP45.1
B46: CE2.46, H2.25, JP46.1
B47: CE2.47, H2.27, JP47.1
B48: CE2.48, H2.29, JP48.1
B49: CE2.49, H2.31, JP49.1
B51: CE2.51, H2.33, JP51.1
GND: CE1.4, CE2.18, CE2.21, CE2.26, CE2.27, CE2.29, CE2.34, CE2.35, CE2.37, CE2.40, CE2.43, CE2.50, H1.2, H1.4, H1.6, H1.8, H1.10, H1.12, H1.14, H1.16, H1.18, H1.20, H1.22, H1.24, H1.26, H1.28, H1.30, H1.32, H1.34, H1.36, H2.2, H2.4, H2.6, H2.8, H2.10, H2.12, H2.14, H2.16, H2.18, H2.20, H2.22, H2.24, H2.26, H2.28, H2.30, H2.32, H2.34, H2.36, J1.4, J1.9, J1.15, J1.18, J1.21, J1.26, J1.27, J1.29, J1.34, J1.35, J1.37, J1.40, J1.43, J1.50, J1.53, J1.54
R1: J1.1, JP1.2
R3: J1.3, JP3.2
R5: J1.5, JP5.2
R6: J1.6, JP6.2
R7: J1.7, JP7.2
R8: J1.8, JP8.2
R10: J1.10, JP10.2
R11: J1.11, JP11.2
R12: J1.12, JP12.2
R13: J1.13, JP13.2
R14: J1.14, JP14.2
R16: J1.16, JP16.2
R17: J1.17, JP17.2
R19: J1.19, JP19.2
R20: J1.20, JP20.2
R22: J1.22, JP22.2
R23: J1.23, JP23.2
R25: J1.25, JP25.2
R28: J1.28, JP28.2
R30: J1.30, JP30.2
R31: J1.31, JP31.2
R32: J1.32, JP32.2
R33: J1.33, JP33.2
R36: J1.36, JP36.2
R38: J1.38, JP38.2
R42: J1.42, JP42.2
R44: J1.44, JP44.2
R45: J1.45, JP45.2, JPX3.2
R46: J1.46, JP46.2
R47: J1.47, JP47.2, JPX5.2
R48: J1.48, JP48.2
R49: J1.49, JP49.2, JPX6.2
R51: J1.51, JP51.2, JPX7.2
V3V3: CE1.2, CE2.24, CE2.39, CE2.41, CE2.52, H2.35, J1.2, J1.24, J1.39, J1.41, J1.52
